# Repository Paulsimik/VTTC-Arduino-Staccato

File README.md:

# VTTC-Arduino-Staccato
Interrupter for VTTC - Kicad project

I'm sharing this interrupter for inspiration if you want to build your own. You may need to modify the wiring diagram or program for proper function. I take no responsibility for any property damage or personal injury.

YouTube #1</br>

YouTube #2</br>

YouTube #3</br>

YouTube #4</br>

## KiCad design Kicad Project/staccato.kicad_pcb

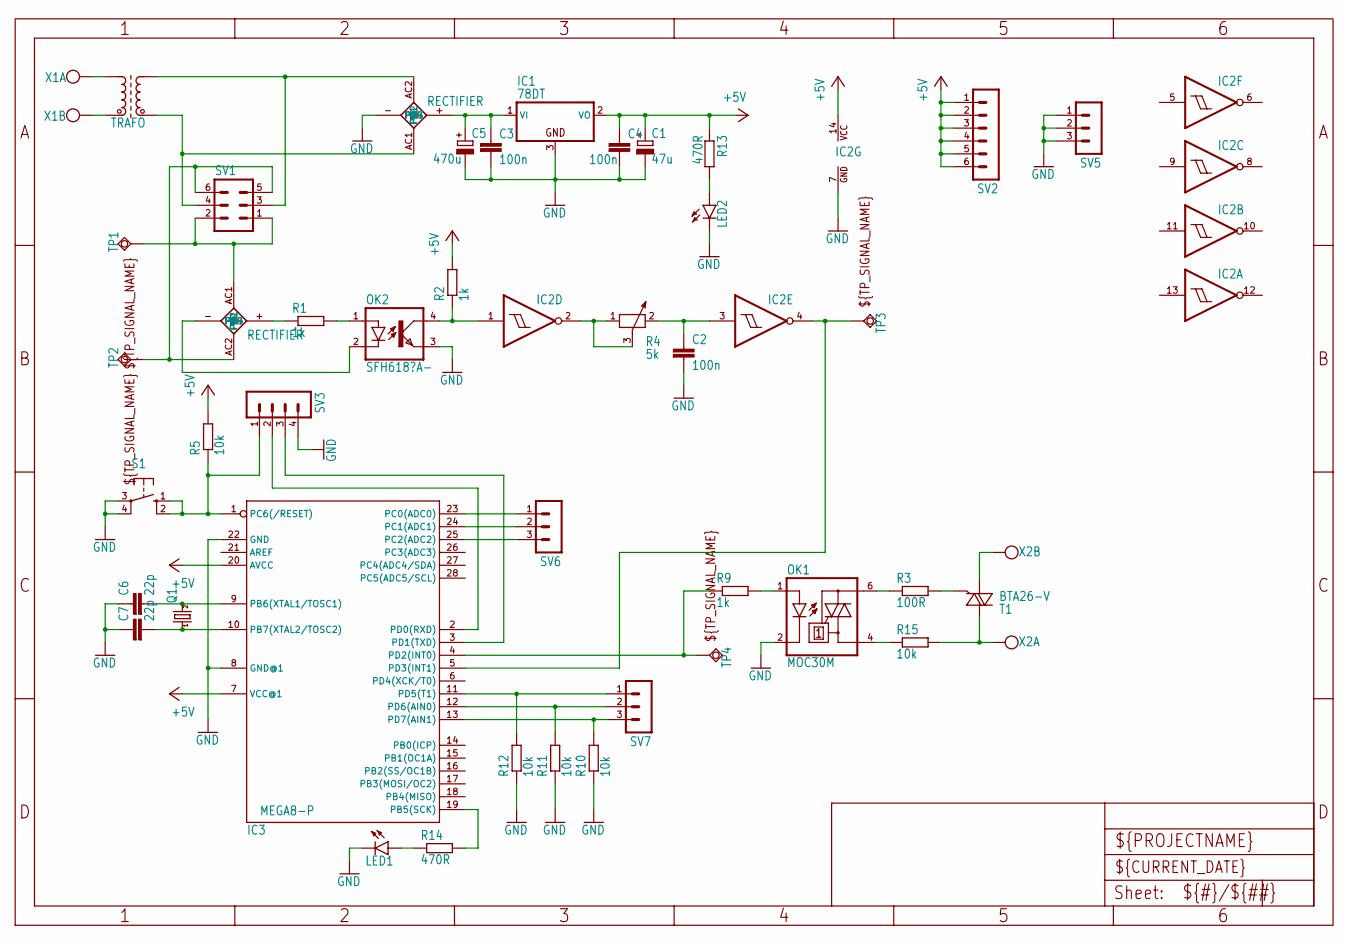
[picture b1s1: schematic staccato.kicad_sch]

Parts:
C1: 47u; E2,5-6
C2: 100n; C050-025X075
C3, C4: 100n; C0805
C5: 470u; E5-10,5
C6, C7: 22p; C0805
IC1: 78DT; TO252
IC2: 7414N; DIL14
IC3: MEGA8-P; DIL28-3
LED1, LED2: LED3MM
OK1: MOC30M; DIL06
OK2: SFH618?A-; DIP4-400
Q1: CRYSTALHC49S; HC49_S
R1, R2, R9: 1k; M0805
R3: 100R; M0805
R4: 5k; PT-10
R5, R10, R11, R12, R15: 10k; M0805
R13, R14: 470R; M0805
S1: 10-XX; B3F-10XX
SV1: MA03-2
SV2: MA06-1
SV3: MA04-1
SV5, SV6, SV7: MA03-1
T1: BTA26-V; TOP3S-1
TP1, TP2, TP3, TP4: TPSQPAD1-13Y; P1-13Y
U$1: TRAFO
U$2, U$4: RECTIFIER
X1, X2: W237-102

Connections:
+5V: C1.+, C4.1, IC1.2 (VO), IC2.14 (VCC), IC3.7 (VCC@1), IC3.20 (AVCC), R2.2, R5.2, R13.1, SV2.1, SV2.2, SV2.3, SV2.4, SV2.5, SV2.6
GND: C1.-, C2.2, C3.2, C4.2, C5.-, C6.1, C7.1, IC1.3 (GND), IC2.7 (GND), IC3.8 (GND@1), IC3.22 (GND), LED1.K (C), LED2.K (C), OK1.2 (C), OK2.3 (EMIT), R10.1, R11.1, R12.1, S1.3, S1.4 (P1), SV3.4, SV5.1, SV5.2, SV5.3, U$2.-
unnamed: SV1.3, U$1.P$3 (A2), U$2.AC2
unnamed: SV1.4, U$1.P$4 (E2), U$2.AC1
unnamed: U$1.P$1 (A1), X1.1
unnamed: U$1.P$2 (E1), X1.2
unnamed: OK2.1 (A), R1.2
unnamed: IC2.1 (I), OK2.4 (COL), R2.1
unnamed: OK1.6 (A2), R3.1
unnamed: R3.2, T1.G
unnamed: R15.2, T1.A2, X2.1
unnamed: T1.A1, X2.2
unnamed: IC2.2 (O), R4.1, R4.3
unnamed: C2.1, IC2.3 (I), R4.2
unnamed: R1.1, U$4.+
unnamed: OK2.2 (C), U$4.-
unnamed: C3.1, C5.+, IC1.1 (VI), U$2.+
unnamed: C6.2, IC3.9 (PB6(XTAL1/TOSC1)), Q1.2
unnamed: IC3.1 (PC6(/RESET)), R5.1, S1.1 (S), S1.2 (S1), SV3.1
unnamed: C7.2, IC3.10 (PB7(XTAL2/TOSC2)), Q1.1
unnamed: IC3.23 (PC0(ADC0)), SV6.1
unnamed: IC3.24 (PC1(ADC1)), SV6.2
unnamed: IC3.25 (PC2(ADC2)), SV6.3
unnamed: OK1.1 (A), R9.2
unnamed: IC3.4 (PD2(INT0)), R9.1, TP4.TP
unnamed: IC3.11 (PD5(T1)), R12.2, SV7.1
unnamed: IC3.12 (PD6(AIN0)), R11.2, SV7.2
unnamed: IC3.13 (PD7(AIN1)), R10.2, SV7.3
unnamed: LED2.A, R13.2
unnamed: IC3.19 (PB5(SCK)), R14.2
unnamed: LED1.A, R14.1
unnamed: SV1.5, SV1.6, TP2.TP, U$4.AC2
unnamed: SV1.1, SV1.2, TP1.TP, U$4.AC1
unnamed: IC2.4 (O), IC3.5 (PD3(INT1)), TP3.TP
unnamed: OK1.4 (A1), R15.1
unnamed: IC3.2 (PD0(RXD)), SV3.2
unnamed: IC3.3 (PD1(TXD)), SV3.3

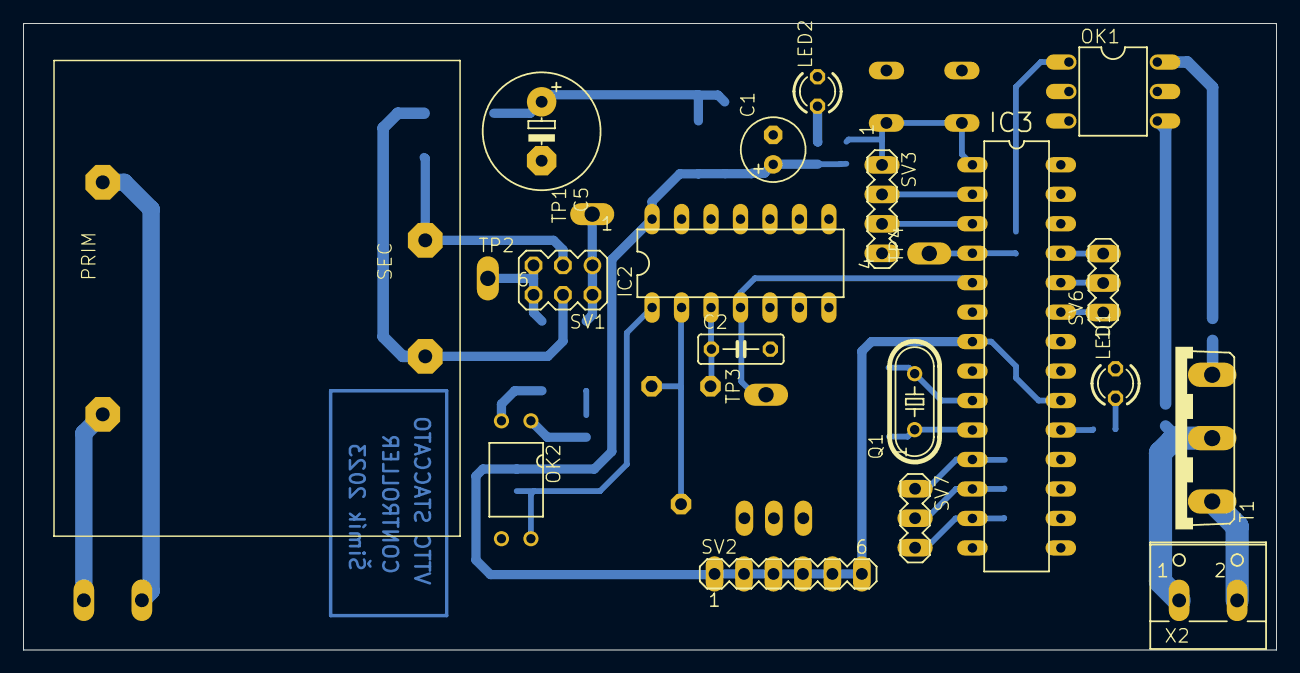
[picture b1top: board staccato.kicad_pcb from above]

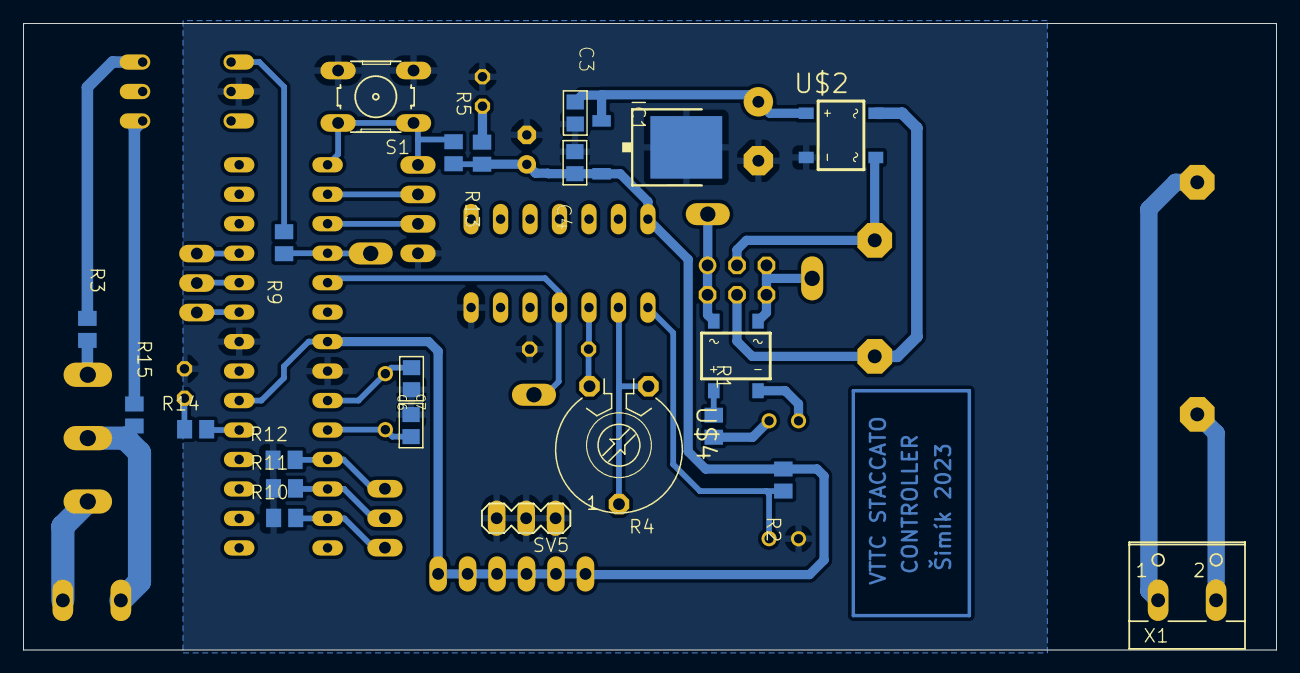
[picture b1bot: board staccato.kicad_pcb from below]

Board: 2 copper layers, 108.0 x 54.0 mm, 44 parts (22 on the bottom side), 37 nets.

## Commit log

2024-11-01 Add Kicad staccato project
